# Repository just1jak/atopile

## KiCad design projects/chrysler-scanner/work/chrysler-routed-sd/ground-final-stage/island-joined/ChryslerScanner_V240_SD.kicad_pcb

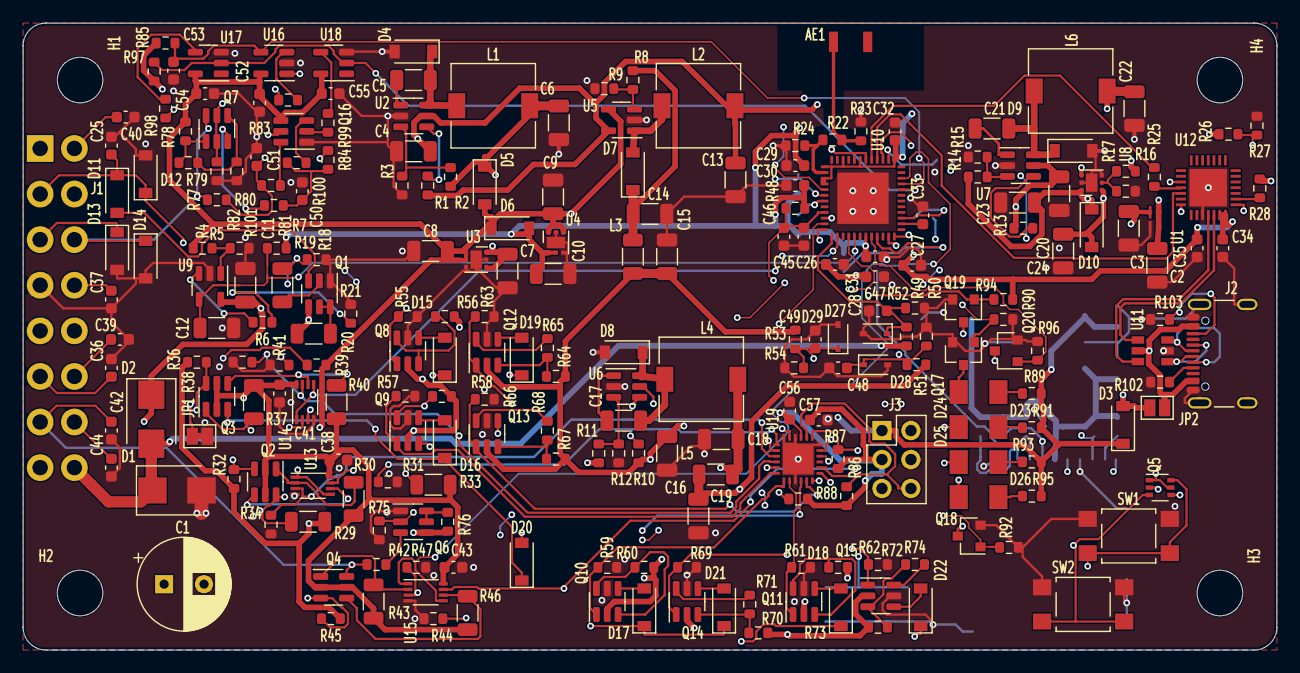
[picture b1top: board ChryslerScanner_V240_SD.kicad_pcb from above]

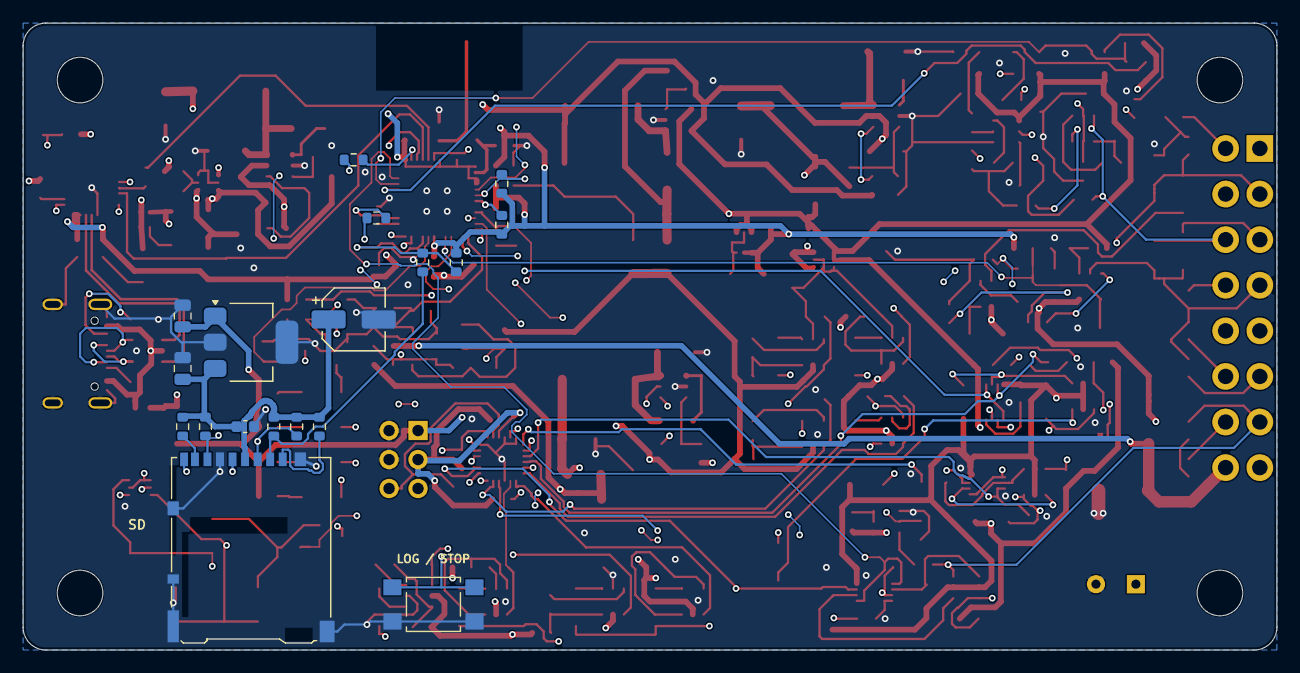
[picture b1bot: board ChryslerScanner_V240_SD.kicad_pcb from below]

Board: 4 copper layers, 110.0 x 55.0 mm, 263 parts (18 on the bottom side), 154 nets.

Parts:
AE1: ANT3216LL00R2400A
C1: 100μF; CP_Radial_D8.0mm_P3.50mm
C2, C3, C4, C7, C9, C13, C15, C16, C19, C20, C23: 10μF; C_1206_3216Metric
C5, C11, C17, C21: 0.1μF; C_1206_3216Metric
C6, C8, C10, C14, C18, C22, C24: 22μF; C_1206_3216Metric
C12: 220pF; C_1206_3216Metric
C25, C36, C37, C39, C40, C42, C44, C50, C51, C53: 220pF; C_0603_1608Metric
C26, C27, C28, C35, C56: 10μF; C_0603_1608Metric
C29, C30, C31, C32, C33, C34, C38, C41, C43, C46, C47, C48, C49, C52, C54, C55, C57: 0.1μF; C_0603_1608Metric
C45: 1μF; C_0603_1608Metric
C58, C59: 10uF; C_0805_2012Metric
C60: 100nF; C_0603_1608Metric
C61: 100uF; CP_Elec_5x5.9
D1: SMBJ30CA; D_SMB
D2: SS56; D_SMB
D3: LMBR130T1G; D_SOD-123
D4, D5, D6, D7, D8, D9, D10: DSK34; D_SOD-123
D11, D15, D16, D17, D18, D19, D20, D21, D22: MSK4005; D_SOD-123
D12, D13, D14: ESD5Z12V; D_SOD-123
D23: RED; LED_V140_Reference
D24: YELLOW; LED_V140_Reference
D25: GREEN; LED_V140_Reference
D26: BLUE; LED_V140_Reference
D27, D28, D29: ESD5Z3V3; D_SOD-323
H1, H2, H3, H4: MountingHole_4mm
J1: 226A-1202; OBDII_ATTEND_226A-1202
J2: USB-C; USB_C_Receptacle_GCT_USB4105-xx-A_16P_TopMnt_Horizontal
J3: I2C; PinHeader_2x03_P2.54mm_Vertical
J4: microSD / DM3AT-SF-PEJM5; microSD_HC_Hirose_DM3AT-SF-PEJM5
JP1: SGND; SolderJumper-2_P1.3mm_Bridged_Pad1.0x1.5mm
JP2: USBPWRBYP; SolderJumper-2_P1.3mm_Open_Pad1.0x1.5mm
L1, L2, L4, L6: 22µH; L_7.3x7.3_H3.5
L3: 240nH; R_1206_3216Metric
L5: 470nH; R_1206_3216Metric
Q1, Q6, Q16: CJ3439KDW; SOT-23-6
Q2, Q3, Q4: 2N7002DW; SOT-23-6
Q5: UMH3N; SOT-363_SC-70-6
Q7: HSSK8811; SOT-23-6
Q8, Q9, Q10, Q11, Q12, Q13, Q14, Q15: HSW4602; SOT-23-6
Q17, Q18, Q19, Q20: AO3400; SOT-23
R1, R10, R13, R14: 100kΩ; R_0603_1608Metric
R2: 68kΩ; R_0603_1608Metric
R3, R6, R12, R15, R17, R18, R21, R31, R34, R38, R41, R44, R47, R48, R55, R57, R59, R61, R63, R66, R69, R72, R75, R77, R83, R84, R90, R92, R94, R96: 10kΩ; R_0603_1608Metric
R4: 2kΩ; R_0603_1608Metric
R5, R7, R28, R32, R36, R39, R56, R58, R60, R62, R64, R67, R70, R73, R76, R85, R86, R87, R88, R97: 4.7kΩ; R_0603_1608Metric
R8: 110kΩ; R_0603_1608Metric
R9: 6.8kΩ; R_0603_1608Metric
R11: 158kΩ; R_0603_1608Metric
R16: 82.5kΩ; R_0603_1608Metric
R19: 360Ω; R_1206_3216Metric
R20: 1kΩ; R_1206_3216Metric
R22: 0Ω; R_0603_1608Metric
R23, R24: nc; R_0603_1608Metric
R25: 499Ω; R_0603_1608Metric
R26: 22kΩ; R_0603_1608Metric
R27: 47kΩ; R_0603_1608Metric
R29, R30, R33, R37, R40, R43, R46: 4.7kΩ; R_1206_3216Metric
R42, R45, R93: 1kΩ; R_0603_1608Metric
R49, R51: 8.66kΩ; R_0603_1608Metric
R50, R52, R54: 1.62kΩ; R_0603_1608Metric
R53: 18.2kΩ; R_0603_1608Metric
R65, R68, R71, R74: 1.1kΩ; R_0603_1608Metric
R78, R80: 13kΩ; R_0603_1608Metric
R79: 120Ω; R_0603_1608Metric
R81, R82: 10Ω; R_0603_1608Metric
R89, R95: 470Ω; R_0603_1608Metric
R91: 300Ω; R_0603_1608Metric
R98, R99: 100Ω; R_0603_1608Metric
R100, R101: 360Ω; R_0603_1608Metric
R102, R103: 5.1kΩ; R_0603_1608Metric
R104, R105, R106: 33R; R_0603_1608Metric
R107, R108, R109, R110, R111, R113, R114: 10k; R_0603_1608Metric
R112: 47k; R_0603_1608Metric
SW1: RESET; SW_SPST_TL3305A
SW2: BOOT; SW_SPST_TL3305A
SW3: LOG / SAFE STOP; SW_SPST_TL3305A
U1: SY6283; SY6283_DFN4
U2, U6, U7: LMR14010; SOT-23-6
U3: TLV76750DRV; WSON-6-1EP_2x2mm_P0.65mm_EP1x1.6mm
U4: TLV76733DRV; WSON-6-1EP_2x2mm_P0.65mm_EP1x1.6mm
U5: LGS6302; SOT-23-5
U8: TLV76701DRV; WSON-6-1EP_2x2mm_P0.65mm_EP1x1.6mm
U9, U16: TS391C; SOT-23-5
U10: ESP32-PICO-V3-02; ESP32_PICO_V3_02
U11: USBLC6-2SC6; USBLC6_V140_Reference
U12: CP2102; CP2102_V140_Reference
U13, U14, U15: 74LVC2G66; VSSOP-8_2.3x2mm_P0.5mm
U17: 74LVC1G17; SOT-23-5
U18: 74LVC1G14; SOT-23-5
U19: AW9523B; AW9523B_QFN24
U20: MCP1825S-3302E/DB; SOT-223-3_TabPin2

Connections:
+3.3V: C10.1, C26.1, C27.1, C28.1, C29.1, C30.1, C31.1, C32.1, C34.1, C35.1, C38.1, C41.1, C43.1, C56.1, C57.1, D6.2, J3.3, Q2.2, Q2.5, Q3.2, Q3.5, Q4.2, Q4.5, R7.1, R28.1, R30.1, R33.2, R37.1, R40.2, R43.1, R46.1, R48.1, R85.1, R86.1, R87.1, R88.1, R94.2, R97.1, R112.1, R113.1, R114.1, U4.1, U4.2, U10.1, U10.3, U10.4, U10.19, U10.37, U10.43, U10.46, U12.6, U12.7, U13.8, U14.8, U15.8, U19.21
+5V: C8.1, C9.1, C52.2, C54.1, C55.1, C58.1, D3.1, D5.2, D6.1, J3.1, Q6.4, Q16.4, R4.1, R29.1, R32.2, R36.1, R39.2, R45.1, R76.1, R78.1, R89.1, R91.1, R93.1, R95.1, U3.1, U3.2, U4.4, U4.6, U5.4, U16.5, U17.5, U18.5, U20.1
+7.5V: C24.1, D10.2, Q1.4, R16.1, R20.1, U8.1
+12V: C1.1, C4.1, C11.2, C13.1, C20.1, D2.1, L2.1, R1.1, R13.1, U2.5, U5.5, U7.5, U9.5
ACT_LED: Q20.1, R96.1, U10.20
CCD+: C50.1, R81.2, R84.1, R100.2
CCD-: C51.1, R82.2, R83.1, R101.2
D+: J2.A6, J2.B6, U11.1
D+P: U11.6, U12.4
D-: J2.A7, J2.B7, U11.3
D-P: U11.4, U12.5
DTR: Q5.2, Q5.4, U12.28
EN: C45.1, C46.1, Q5.6, R48.2, SW1.2, U10.9
GND: C1.2, C2.2, C3.2, C4.2, C6.2, C7.2, C8.2, C9.2, C10.2, C11.1, C12.2, C13.2, C14.2, C15.2, C16.2, C18.2, C19.2, C20.2, C22.2, C23.2, C24.2, C25.2, C26.2, C27.2, C28.2, C29.2, C30.2, C31.2, C32.2, C33.2, C34.2, C35.2, C36.1, C37.1, C38.2, C39.1, C40.1, C41.2, C42.2, C43.2, C44.2, C45.2, C46.2, C47.2, C48.2, C49.2, C50.2, C51.2, C52.1, C53.2, C54.2, C55.2, C56.2, C57.2, C58.2, C59.2, C60.2, C61.2, D1.2, D4.2, D8.2, D9.2, D12.2, D13.2, D14.2, D27.2, D28.2, D29.2, J1.4, J2.A1, J2.A12, J2.B1, J2.B12, J2.SH, J3.2, J3.4, J4.6, J4.10, J4.SH, JP1.2, Q1.1, Q6.1, Q8.5, Q9.5, Q10.5, Q11.5, Q12.5, Q13.5, Q14.5, Q15.5, Q16.1, Q17.2, Q18.2, Q19.2, Q20.2, R3.2, R5.2, R9.2, R12.2, R15.2, R17.2, R18.2, R21.2, R23.2, R24.2, R27.2, R31.1, R34.2, R38.1, R41.2, R44.1, R47.1, R50.2, R52.2, R54.2, R55.2, R57.2, R59.2, R61.2, R63.2, R66.2, R69.2, R72.2, R75.2, R77.1, R80.2, R90.2, R92.2, R96.2, R102.2, R103.2, SW1.1, SW2.1, SW3.2, U1.1, U2.2, U3.3, U3.5, U3.7, U4.3, U4.5, U4.7, U5.2, U6.2, U7.2, U8.3, U8.5, U8.7, U9.2, U10.49, U11.2, U12.3, U12.29, U13.4, U14.4, U15.4, U16.2, U17.3, U18.3, U19.9, U19.18, U19.22, U19.24, U19.25, U20.2
IO0: Q5.3, SW2.2, U10.23
J1962-2: C25.1, D11.1, D12.1, J1.2, R6.1, R21.1
J1962-3: D13.1, J1.3, Q7.3, R81.1
J1962-6: C36.2, D15.1, D19.1, J1.6, Q2.6, R29.2
J1962-7: C42.1, J1.7, Q4.6, R42.2
J1962-9: C40.2, D16.1, D20.1, J1.9, Q3.3, R39.1
J1962-11: D14.1, J1.11, Q7.6, R82.1
J1962-12: C37.2, D17.1, D21.1, J1.12, Q2.3, R32.1
J1962-14: C39.2, D18.1, D22.1, J1.14, Q3.6, R36.2
J1962-15: C44.1, J1.15, Q4.3, R45.2
J1962-16: D1.1, D2.2, J1.16, R49.1
LNA_IN: R22.2, R24.1, U10.2
LOG_BUTTON: R113.2, SW3.1, U10.6
MCU_SD_CS: R106.1, R112.2, U10.21
MCU_SD_MOSI: R105.1, U10.27
MCU_SD_SCK: R104.1, U10.38
N_C3_1: C3.1, D3.2, JP2.2, U1.4
N_C5_1: C5.1, U2.1
N_C5_2: C5.2, D4.1, L1.1, U2.6
N_C17_1: C17.1, U6.1
N_C17_2: C17.2, D8.1, L4.1, U6.6
N_C21_1: C21.1, U7.1
N_C21_2: C21.2, D9.1, L6.1, U7.6
N_C33_1: C33.1, U10.26
N_D7_2: D7.2, L2.2, U5.1
N_J1_5: J1.5, JP1.1
N_Q1B_3: D11.2, Q1.3
N_Q8B_4: D15.2, Q8.4
N_Q9B_4: D16.2, Q9.4
N_Q10B_4: D17.2, Q10.4
N_Q11B_4: D18.2, Q11.4
N_Q12B_4: D19.2, Q12.4
N_Q13B_4: D20.2, Q13.4
N_Q14B_4: D21.2, Q14.4
N_Q15B_4: D22.2, Q15.4
N_Q17_3: D23.1, Q17.3
N_Q18_3: D24.1, Q18.3
N_Q19_3: D25.1, Q19.3
N_Q20_3: D26.1, Q20.3
N_R1_2: R1.2, U2.4
N_R2_1: C6.1, C7.1, D5.1, L1.2, R2.1, U3.4, U3.6
N_R3_1: R2.2, R3.1, U2.3
N_R4_2: R4.2, R5.1, U9.1
N_R6_2: R6.2, U9.3
N_R8_1: C14.1, D7.1, L3.1, R8.1
N_R8_2: R8.2, R9.1, U5.3
N_R10_2: R10.2, U6.4
N_R11_1: C18.1, L4.2, L5.1, R11.1
N_R11_2: R11.2, R12.1, U6.3
N_R13_2: R13.2, U7.4
N_R14_1: C22.1, C23.1, D10.1, L6.2, R14.1, U8.4, U8.6
N_R14_2: R14.2, R15.1, U7.3
N_R16_2: R16.2, R17.1, U8.2
N_R19_2: Q1.2, R19.2
N_R20_2: Q1.5, Q1.6, R20.2
N_R23_1: AE1.1, R22.1, R23.1
N_R25_1: R25.1, U10.41
N_R26_2: R26.2, R27.1, U12.8
N_R28_2: R28.2, U12.9
N_R30_2: Q2.1, R30.2, U13.2
N_R33_1: Q2.4, R33.1, U13.6
N_R37_2: Q3.1, R37.2, U14.2
N_R40_1: Q3.4, R40.1, U14.6
N_R43_2: Q4.1, R43.2, U15.2
N_R46_2: Q4.4, R46.2, U15.6
N_R56_2: Q8.3, Q8.6, R56.2
N_R58_2: Q9.3, Q9.6, R58.2
N_R60_2: Q10.3, Q10.6, R60.2
N_R62_2: Q11.3, Q11.6, R62.2
N_R64_2: Q12.3, R64.2, R65.1
N_R65_2: Q12.6, R65.2
N_R67_2: Q13.3, R67.2, R68.1
N_R68_2: Q13.6, R68.2
N_R70_2: Q14.3, R70.2, R71.1
N_R71_2: Q14.6, R71.2
N_R73_2: Q15.3, R73.2, R74.1
N_R74_2: Q15.6, R74.2
N_R76_2: Q6.5, Q6.6, R76.2
N_R78_2: Q7.1, R78.2, R79.1
N_R79_2: Q7.4, R79.2, R80.1
N_R83_2: R83.2, U16.3
N_R84_2: R84.2, U16.1
N_R88_2: R88.2, U19.23
N_R89_2: D23.2, R89.2
N_R91_2: D24.2, R91.2
N_R93_2: D25.2, R93.2
N_R95_2: D26.2, R95.2
N_R98_1: R98.1, U17.4
N_R98_2: Q16.5, R98.2
N_R99_1: R99.1, U18.4
N_R99_2: Q16.2, R99.2
N_R100_1: Q16.3, R100.1
N_R101_1: Q16.6, R101.1
PCI_RX: C12.1, R7.2, U9.4, U10.17
PCI_TX: R18.1, R19.1, U10.16
PWR_LED: Q19.1, R94.1, U10.12
RTS: Q5.1, Q5.5, U12.24
RX0: U10.40, U12.26
RX1: C53.1, R85.2, U10.33, U16.4
RX2: U10.34, U15.1, U15.5
RX7_BIAS: Q6.3, R42.1
RX7_BIAS_EN: Q6.2, R75.1, U19.16
RX7_EN: R44.2, U15.7, U19.14
RX15_EN: R47.2, U15.3, U19.15
RX_LED: Q17.1, R90.1, U10.14
SCL: J3.5, R87.2, U10.39, U19.19
SDA: J3.6, R86.2, U10.42, U19.20
SD_3V3: C59.1, C60.1, C61.1, J4.4, R107.1, R108.1, R109.1, R110.1, R111.1, U20.3
SD_CS: J4.2, R106.2, R107.2
SD_DAT1: J4.8, R110.2
SD_DAT2: J4.1, R111.2
SD_DETECT: J4.9, R114.2, U10.7
SD_MISO: J4.7, R109.2, U10.5
SD_MOSI: J4.3, R105.2, R108.2
SD_SCK: J4.5, R104.2
TBEN: Q7.2, Q7.5, R77.2, U19.17
TX0: R25.2, U12.25
TX1: R97.2, U10.32, U17.2, U18.2
TX2: U10.24, U13.1, U13.5, U14.1, U14.5
TX6_EN: R31.2, U13.7, U19.1
TX9_EN: R41.1, U14.3, U19.2
TX12_EN: R34.1, U13.3, U19.3
TX14_EN: R38.2, U14.7, U19.4
TX_LED: Q18.1, R92.1, U10.15
USB_CC1: J2.A5, R102.1
USB_CC2: J2.B5, R103.1
VBB: C19.1, L5.2, Q8.2, Q9.2, Q10.2, Q11.2, R51.1, R56.1, R58.1, R60.1, R62.1
VBB_TO_TX6: Q8.1, R55.1, U19.5
VBB_TO_TX9: Q9.1, R57.1, U19.6
VBB_TO_TX12: Q10.1, R59.1, U19.7
VBB_TO_TX14: Q11.1, R61.1, U19.8
VBUS: C2.1, J2.A4, J2.A9, J2.B4, J2.B9, JP2.1, R26.1, U1.2, U1.3, U11.5
VPP: C15.1, C16.1, L3.2, Q12.2, Q13.2, Q14.2, Q15.2, R10.1, R53.1, R64.1, R67.1, R70.1, R73.1, U6.5
VPP_TO_TX6: Q12.1, R63.1, U19.10
VPP_TO_TX9: Q13.1, R66.1, U19.11
VPP_TO_TX12: Q14.1, R69.1, U19.12
VPP_TO_TX14: Q15.1, R72.1, U19.13
V_BA: C47.1, D27.1, R49.2, R50.1, U10.13
V_BT: C48.1, D28.1, R51.2, R52.1, U10.10
V_PR: C49.1, D29.1, R53.2, R54.1, U10.11

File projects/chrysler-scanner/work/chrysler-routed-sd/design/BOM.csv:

"References","Value","Footprint","Quantity","DNP","Datasheet","Description"
"AE1","ANT3216LL00R2400A","footprints:ANT3216LL00R2400A","1","","",""
"C1","100μF","footprints:CP_Radial_D8.0mm_P3.50mm","1","","",""
"C2-C4,C7,C9,C13,C15,C16,C19,C20,C23","10μF","footprints:C_1206_3216Metric","11","","",""
"C5,C11,C17,C21","0.1μF","footprints:C_1206_3216Metric","4","","",""
"C6,C8,C10,C14,C18,C22,C24","22μF","footprints:C_1206_3216Metric","7","","",""
"C12","220pF","footprints:C_1206_3216Metric","1","","",""
"C25,C36,C37,C39,C40,C42,C44,C50,C51,C53","220pF","footprints:C_0603_1608Metric","10","","",""
"C26-C28,C35,C56","10μF","footprints:C_0603_1608Metric","5","","",""
"C29-C34,C38,C41,C43,C46-C49,C52,C54,C55,C57","0.1μF","footprints:C_0603_1608Metric","17","","",""
"C45","1μF","footprints:C_0603_1608Metric","1","","",""
"C58,C59","10uF","Capacitor_SMD:C_0805_2012Metric","2","","","10V X7R ceramic"
"C60","100nF","Capacitor_SMD:C_0603_1608Metric","1","","","10V X7R ceramic"
"C61","100uF","Capacitor_SMD:CP_Elec_5x5.9","1","","","Bulk capacitor does not provide safe power-off hold-up"
"D1","SMBJ30CA","footprints:D_SMB","1","","",""
"D2","SS56","footprints:D_SMB","1","","",""
"D3","LMBR130T1G","footprints:D_SOD-123","1","","",""
"D4-D10","DSK34","footprints:D_SOD-123","7","","",""
"D11,D15-D22","MSK4005","footprints:D_SOD-123","9","","",""
"D12-D14","ESD5Z12V","footprints:D_SOD-123","3","","",""
"D23","RED","footprints:LED_V140_Reference","1","","",""
"D24","YELLOW","footprints:LED_V140_Reference","1","","",""
"D25","GREEN","footprints:LED_V140_Reference","1","","",""
"D26","BLUE","footprints:LED_V140_Reference","1","","",""
"D27-D29","ESD5Z3V3","footprints:D_SOD-323","3","","",""
"J1","226A-1202","footprints:OBDII_ATTEND_226A-1202","1","","",""
"J2","USB-C","footprints:USB_C_Receptacle_GCT_USB4105-xx-A_16P_TopMnt_Horizontal","1","","",""
"J3","I2C","footprints:PinHeader_2x03_P2.54mm_Vertical","1","","",""
"J4","microSD / DM3AT-SF-PEJM5","Connector_Card:microSD_HC_Hirose_DM3AT-SF-PEJM5","1","","","On-board push-push microSD socket, rear edge access"
"L1,L2,L4,L6","22µH","footprints:L_7.3x7.3_H3.5","4","","",""
"L3","240nH","footprints:R_1206_3216Metric","1","","",""
"L5","470nH","footprints:R_1206_3216Metric","1","","",""
"Q1,Q6,Q16","CJ3439KDW","footprints:SOT-23-6","3","","",""
"Q2-Q4","2N7002DW","footprints:SOT-23-6","3","","",""
"Q5","UMH3N","footprints:SOT-363_SC-70-6","1","","",""
"Q7","HSSK8811","footprints:SOT-23-6","1","","",""
"Q8-Q15","HSW4602","footprints:SOT-23-6","8","","",""
"Q17-Q20","AO3400","footprints:SOT-23","4","","",""
"R1,R10,R13,R14","100kΩ","footprints:R_0603_1608Metric","4","","",""
"R2","68kΩ","footprints:R_0603_1608Metric","1","","",""
"R3,R6,R12,R15,R17,R18,R21,R31,R34,R38,R41,R44,R47,R48,R55,R57,R59,R61,R63,R66,R69,R72,R75,R77,R83,R84,R90,R92,R94,R96","10kΩ","footprints:R_0603_1608Metric","30","","",""
"R4","2kΩ","footprints:R_0603_1608Metric","1","","",""
"R5,R7,R28,R32,R36,R39,R56,R58,R60,R62,R64,R67,R70,R73,R76,R85-R88,R97","4.7kΩ","footprints:R_0603_1608Metric","20","","",""
"R8","110kΩ","footprints:R_0603_1608Metric","1","","",""
"R9","6.8kΩ","footprints:R_0603_1608Metric","1","","",""
"R11","158kΩ","footprints:R_0603_1608Metric","1","","",""
"R16","82.5kΩ","footprints:R_0603_1608Metric","1","","",""
"R19","360Ω","footprints:R_1206_3216Metric","1","","",""
"R20","1kΩ","footprints:R_1206_3216Metric","1","","",""
"R22","0Ω","footprints:R_0603_1608Metric","1","","",""
"R23,R24","nc","footprints:R_0603_1608Metric","2","DNP","",""
"R25","499Ω","footprints:R_0603_1608Metric","1","","",""
"R26","22kΩ","footprints:R_0603_1608Metric","1","","",""
"R27","47kΩ","footprints:R_0603_1608Metric","1","","",""
"R29,R30,R33,R37,R40,R43,R46","4.7kΩ","footprints:R_1206_3216Metric","7","","",""
"R42,R45,R93","1kΩ","footprints:R_0603_1608Metric","3","","",""
"R49,R51","8.66kΩ","footprints:R_0603_1608Metric","2","","",""
"R50,R52,R54","1.62kΩ","footprints:R_0603_1608Metric","3","","",""
"R53","18.2kΩ","footprints:R_0603_1608Metric","1","","",""
"R65,R68,R71,R74","1.1kΩ","footprints:R_0603_1608Metric","4","","",""
"R78,R80","13kΩ","footprints:R_0603_1608Metric","2","","",""
"R79","120Ω","footprints:R_0603_1608Metric","1","","",""
"R81,R82","10Ω","footprints:R_0603_1608Metric","2","","",""
"R89,R95","470Ω","footprints:R_0603_1608Metric","2","","",""
"R91","300Ω","footprints:R_0603_1608Metric","1","","",""
"R98,R99","100Ω","footprints:R_0603_1608Metric","2","","",""
"R100,R101","360Ω","footprints:R_0603_1608Metric","2","","",""
"R102,R103","5.1kΩ","footprints:R_0603_1608Metric","2","","",""
"R104-R106","33R","Resistor_SMD:R_0603_1608Metric","3","","","SPI series resistor; place close to U10 source pin"
"R107-R111","10k","Resistor_SMD:R_0603_1608Metric","5","","",""
"R112","47k","Resistor_SMD:R_0603_1608Metric","1","","","GPIO15 strap and inactive CS; supply referenced to MCU rail"
"R113,R114","10k","Resistor_SMD:R_0603_1608Metric","2","","","External pullup required for ESP32 input-only GPIO"
"SW1","RESET","footprints:SW_SPST_TL3305A","1","","",""
"SW2","BOOT","footprints:SW_SPST_TL3305A","1","","",""
"SW3","LOG / SAFE STOP","footprints:SW_SPST_TL3305A","1","","","Debounced firmware-controlled logging toggle, GPIO37"
"U1","SY6283","footprints:SY6283_DFN4","1","","",""
"U2,U6,U7","LMR14010","footprints:SOT-23-6","3","","",""
"U3","TLV76750DRV","footprints:WSON-6-1EP_2x2mm_P0.65mm_EP1x1.6mm","1","","",""
"U4","TLV76733DRV","footprints:WSON-6-1EP_2x2mm_P0.65mm_EP1x1.6mm","1","","",""
"U5","LGS6302","footprints:SOT-23-5","1","","",""
"U8","TLV76701DRV","footprints:WSON-6-1EP_2x2mm_P0.65mm_EP1x1.6mm","1","","",""
"U9,U16","TS391C","footprints:SOT-23-5","2","","",""
"U10","ESP32-PICO-V3-02","footprints:ESP32_PICO_V3_02","1","","",""
"U11","USBLC6-2SC6","footprints:USBLC6_V140_Reference","1","","",""
"U12","CP2102","footprints:CP2102_V140_Reference","1","","",""
"U13-U15","74LVC2G66","footprints:VSSOP-8_2.3x2mm_P0.5mm","3","","",""
"U17","74LVC1G17","footprints:SOT-23-5","1","","",""
"U18","74LVC1G14","footprints:SOT-23-5","1","","",""
"U19","AW9523B","footprints:AW9523B_QFN24","1","","",""
"U20","MCP1825S-3302E/DB","Package_TO_SOT_SMD:SOT-223-3_TabPin2","1","","","Dedicated 500mA SD rail; main +5V total budget still applies"
